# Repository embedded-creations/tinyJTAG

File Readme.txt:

tinyJTAG is a modification of the USBasp project to program via JTAG
instead of SPI or TPI, and to run on the ATtiny85.  

LICENSE
tinyJTAG is distributed under the terms and conditions of the GNU GPL version
2 (see "firmware/usbdrv/License.txt" for details).

CAUTIONS

Hardware:
All 6 IO pins of the ATtiny85 are used, including the reset pin.  The 
RSTDISBL fuse needs to be programmed to disable external reset funcionality
and enable use of the reset pin as IO.  After programming the fuse the part
can only be programmed through a high-voltage programmmer, or through the 
USBaspLoader-tiny85 boot loader.  The project is intended to be used in
conjunction with the USBaspLoader-tiny85 boot loader, and so doesn't include
an easy way to disable the external reset fuse in the makefile.  The 
USBaspLoader-tiny85 boot loader should be loaded on to the part first, tested
to make sure it was flashed properly, then the reset fuse can be disabled and 
the tinyJTAG firmware loaded through AVRDUDE.

Use:
If loading the the precompiled binary with bootloader, the bootloader will identify itself as a USBasp
programmer with an ATtiny85 target for five seconds before starting the 
tinyJTAG programmer, which will identify itself as a USBasp programmer.  
Wait for five seconds after connecting the tinyJTAG programmer to USB before
using AVRDUDE to connect to the JTAG target.  Be especially cautious when programming
ATtiny85 targets that you are connected to the tinyJTAG application and 
not the bootloader, as you could inadvertently erase the tinyJTAG application.

USE PRECOMPILED VERSION
Firmware:
Set the fuses and load USBaspLoader-tiny85 onto the tiny85 using your programmer of choice
- "make fuses" and "make flash" in USBaspLoader-tiny85\firmware directory
Verify that the boot loader was loaded correctly and that AVRDUDE can connect to it
- a signature read in AVRDUDE should show the ATtiny85 fuses
When you're sure you're ready, disable the external reset fuse on the tiny85
- see "CAUTIONS" in the USBaspLoader-tiny85 project
- "make disablereset" in USBaspLoader-tiny85\firmware directory
Load the tinyJTAG firmware
- "make flash" in tinyJTAG/firmware directory

There are no jumpers that need to be set for programming with an external programmer

BUILDING AND INSTALLING FROM SOURCE CODE

Firmware:
...

For more information on the tinyJTAG programmer, please visit the
following URL:

http://www.embedded-creations.com

(c) 2012 Louis Beaudoin

Below is the unmodified README file for USBasp:

=========================================================================

This is the README file for USBasp.

USBasp is a USB in-circuit programmer for Atmel AVR controllers. It simply
consists of an ATMega88 or an ATMega8 and a couple of passive components.
The programmer uses a firmware-only USB driver, no special USB controller
is needed.

Features:
- Works under multiple platforms. Linux, Mac OS X and Windows are tested.
- No special controllers or smd components are needed.
- Programming speed is up to 5kBytes/sec.
- SCK option to support targets with low clock speed (< 1,5MHz).
- Planned: serial interface to target (e.g. for debugging).

LICENSE

USBasp is distributed under the terms and conditions of the GNU GPL version
2 (see "firmware/usbdrv/License.txt" for details).

USBasp is built with V-USB driver by OBJECTIVE DEVELOPMENT GmbH. See
"firmware/usbdrv/" for further information.

LIMITATIONS

Hardware:
This package includes a circuit diagram. This circuit can only be used for
programming 5V target systems. For other systems a level converter is needed.

Firmware:
The firmware dosn't support USB Suspend Mode. A bidirectional serial
interface to slave exists in hardware but the firmware doesn't support it yet.

USE PRECOMPILED VERSION

Firmware:
Flash "bin/firmware/usbasp.atmega88.xxxx-xx-xx.hex" or
"bin/firmware/usbasp.atmega8.xxxx-xx-xx.hex" to the used controller with a
working programmer (e.g. with avrdude, uisp, ...). Set jumper J2 to activate
USBasp firmware update function.
You have to change the fuse bits for external crystal (see "make fuses").
# TARGET=atmega8    HFUSE=0xc9  LFUSE=0xef
# TARGET=atmega48   HFUSE=0xdd  LFUSE=0xff
# TARGET=atmega88   HFUSE=0xdd  LFUSE=0xff

Windows:
Start Windows and connect USBasp to the system. When Windows asks for a
driver, choose "bin/win-driver". On Win2k and WinXP systems, Windows will
warn that the driver is is not 'digitally signed'. Ignore this message and
continue with the installation.
Now you can run avrdude. Examples:
1. Enter terminal mode with an AT90S2313 connected to the programmer:
   avrdude -c usbasp -p at90s2313 -t
2. Write main.hex to the flash of an ATmega8:
   avrdude -c usbasp -p atmega8 -U flash:w:main.hex

Setting jumpers:
J1 Power target
   Supply target with 5V (USB voltage). Be careful with this option, the
   circuit isn't protected against short circuit!
J2 Jumper for firmware upgrade (not self-upgradable)
   Set this jumper for flashing the ATMega(4)8 of USBasp with another working
   programmer.
J3 SCK option
   If the target clock is lower than 1,5 MHz, you have to set this jumper.
   Then SCK is scaled down from 375 kHz to about 8 kHz.

BUILDING AND INSTALLING FROM SOURCE CODE

Firmware:
To compile the firmware
1. install the GNU toolchain for AVR microcontrollers (avr-gcc, avr-libc),
2. change directory to firmware/
3. run "make main.hex"
4. flash "main.hex" to the ATMega(4)8. E.g. with uisp or avrdude (check
the Makefile option "make flash"). To flash the firmware you have
to set jumper J2 and connect USBasp to a working programmer.
You have to change the fuse bits for external crystal, (check the Makefile
option "make fuses").

Software (avrdude):
AVRDUDE supports USBasp since version 5.2. 
1. install libusb: http://libusb.sourceforge.net/
2. get latest avrdude release: http://download.savannah.gnu.org/releases/avrdude/
3. cd avrdude-X.X.X
5. configure to your environment:
   ./bootstrap (I had to comment out the two if-blocks which verify the
                installed versions of autoconf and automake)
   ./configure
6. compile and install it:
   make 
   make install

Notes on Windows (Cygwin):
Download libusb-win32-device-bin-x.x.x.x.tar.gz from
http://libusb-win32.sourceforge.net/ and unpack it.
-> copy lib/gcc/libusb.a to lib-path
-> copy include/usb.h to include-path
cd avrdude
./configure LDFLAGS="-static" --enable-versioned-doc=no
make

Notes on Darwin/MacOS X:
after "./configure" I had to edit Makefile:
change "avrdude_CPPFLAGS" to "AM_CPPFLAGS"
(why is this needed only on mac? bug in configure.ac?)

Notes on Linux:
To use USBasp as non-root, you have to define some device rules. See
bin/linux-nonroot for an example.

FILES IN THE DISTRIBUTION

Readme.txt ...................... The file you are currently reading
firmware ........................ Source code of the controller firmware
firmware/usbdrv ................. AVR USB driver by Objective Development
firmware/usbdrv/License.txt ..... Public license for AVR USB driver and USBasp
circuit ......................... Circuit diagram in PDF and EAGLE format
bin ............................. Precompiled programs
bin/win-driver .................. Windows driver
bin/firmware .................... Precompiled firmware
bin/linux-nonroot ............... Linux device rule file

MORE INFORMATION

For more information on USBasp and it's components please visit the
following URLs:

USBasp .......................... http://www.fischl.de/usbasp/

Firmware-only V-USB driver ...... http://www.obdev.at/products/vusb/
avrdude ......................... http://www.nongnu.org/avrdude/
libusb .......................... http://libusb.sourceforge.net/
libusb-win32 .................... http://libusb-win32.sourceforge.net/

2011-05-28 Thomas Fischl <tfischl@gmx.de>
http://www.fischl.de

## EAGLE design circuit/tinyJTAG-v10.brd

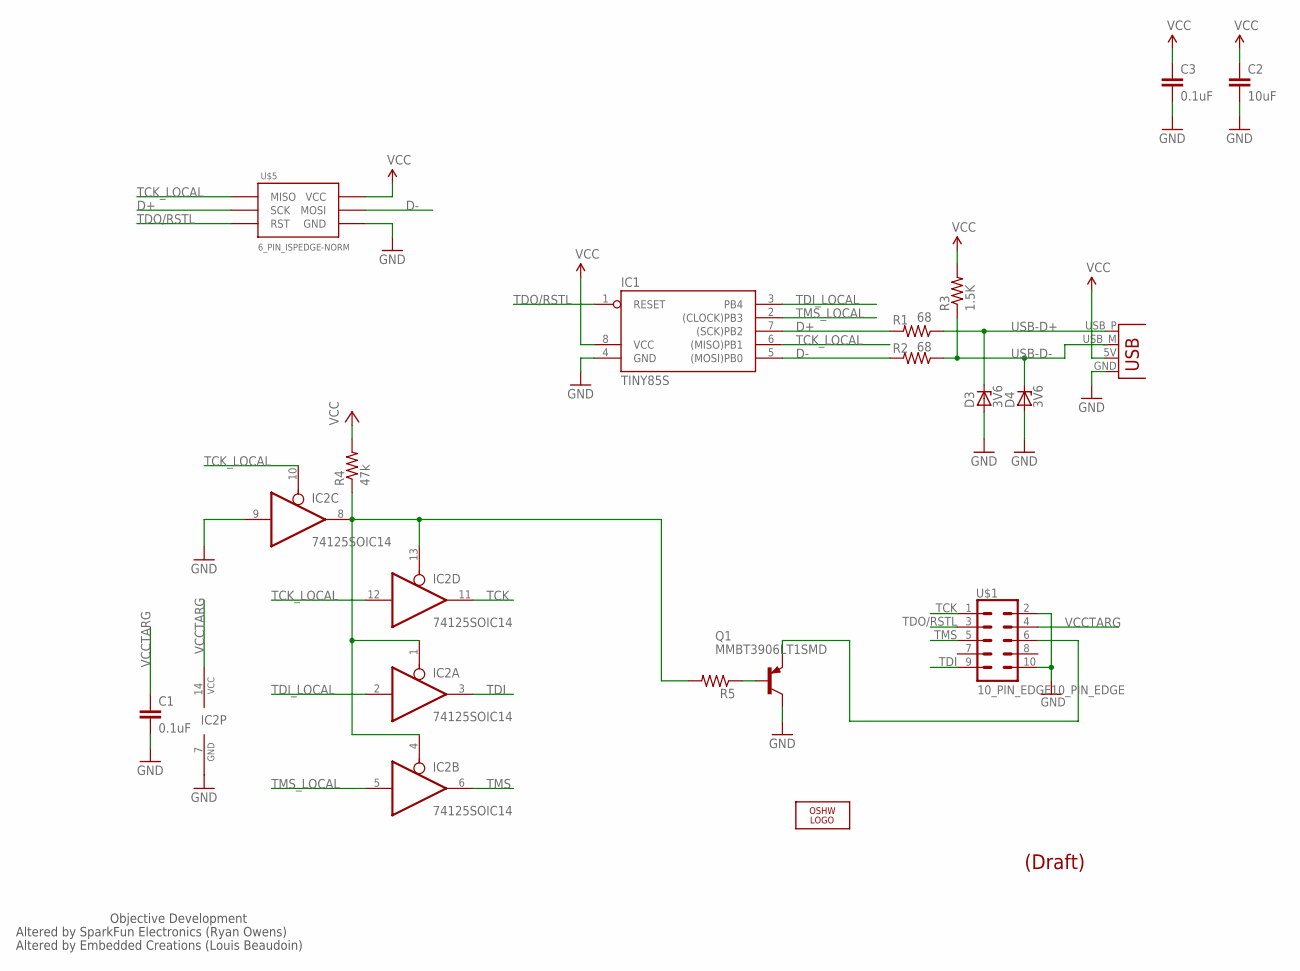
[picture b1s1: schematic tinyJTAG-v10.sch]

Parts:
C1, C3: 0.1uF; 0603-CAP
C2: 10uF; C0805
D3, D4: 3V6; DIODE_SOD323-W
IC1: TINY85S; SOIC8
IC2: 74125SOIC14; SO14
LOGO1: OSHW_LOGO_FILLX0150-NT; OSHW_FILLX150_NOTEXT
Q1: MMBT3906LT1SMD; SOT23-BEC
R1, R2: 68; 0603-RES
R3: 1.5K; 0603-RES
R4: 47k; 0603-RES
R5: RESISTOR0603-RES; 0603-RES
U$1: 10_PIN_EDGE10_PIN_EDGE; 10_PIN_EDGE
U$5: 6_PIN_ISPEDGE-NORM; 6_PIN_EDGE
X1: USBPCB; USB-A-PCB

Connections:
D+: IC1.7 ((SCK)PB2), R1.2, U$5.3 (SCK)
D-: IC1.5 ((MOSI)PB0), R2.2, U$5.4 (MOSI)
GND: C1.2, C2.2, C3.2, D3.A, D4.A, IC1.4 (GND), IC2.7 (GND), IC2.9 (I), Q1.C, U$1.2, U$1.10, U$5.6 (GND), X1.GND
unnamed: IC2.1 (OE), IC2.4 (OE), IC2.8 (O), IC2.13 (OE), R4.1, R5.2
unnamed: Q1.E, U$1.6
unnamed: Q1.B, R5.1
TCK: IC2.11 (O), U$1.1
TCK_LOCAL: IC1.6 ((MISO)PB1), IC2.10 (OE), IC2.12 (I), U$5.1 (MISO)
TDI: IC2.3 (O), U$1.9
TDI_LOCAL: IC1.3 (PB4), IC2.2 (I)
TDO/RSTL: IC1.1 (RESET), U$1.3, U$5.5 (RST)
TMS: IC2.6 (O), U$1.5
TMS_LOCAL: IC1.2 ((CLOCK)PB3), IC2.5 (I)
USB-D+: D3.C, R1.1, X1.USB_P (D+)
USB-D-: D4.C, R2.1, R3.1, X1.USB_M (D-)
VCC: C2.1, C3.1, IC1.8 (VCC), R3.2, R4.2, U$5.2 (VCC), X1.5V (VBUS)
VCCTARG: C1.1, IC2.14 (VCC), U$1.4

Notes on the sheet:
Objective Development
Altered by SparkFun Electronics (Ryan Owens)
Altered by Embedded Creations (Louis Beaudoin)
(Draft)

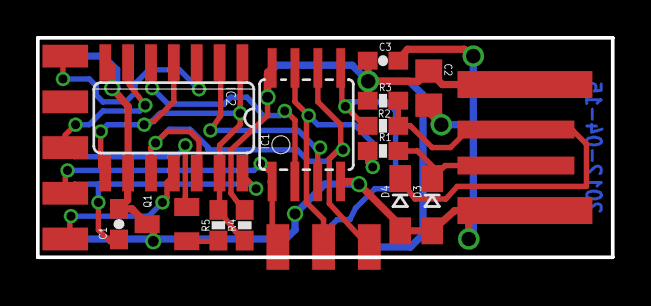
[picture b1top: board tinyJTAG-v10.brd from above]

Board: 2 copper layers, 31.9 x 12.2 mm, 17 parts (1 on the bottom side), 17 nets.

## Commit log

2012-04-09 added CC info back
2012-04-14 added "draft" to title
2012-05-11 Version sent for manufacturing initial prototypes
2012-05-11 cleaned up CC license and made visible
2014-01-05 Fixed typo

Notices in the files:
circuit/tinyJTAG-v10.brd:
Released under the Creative Commons Attribution Share-Alike 3.0 License
http://creativecommons.org/licenses/by-sa/3.0
